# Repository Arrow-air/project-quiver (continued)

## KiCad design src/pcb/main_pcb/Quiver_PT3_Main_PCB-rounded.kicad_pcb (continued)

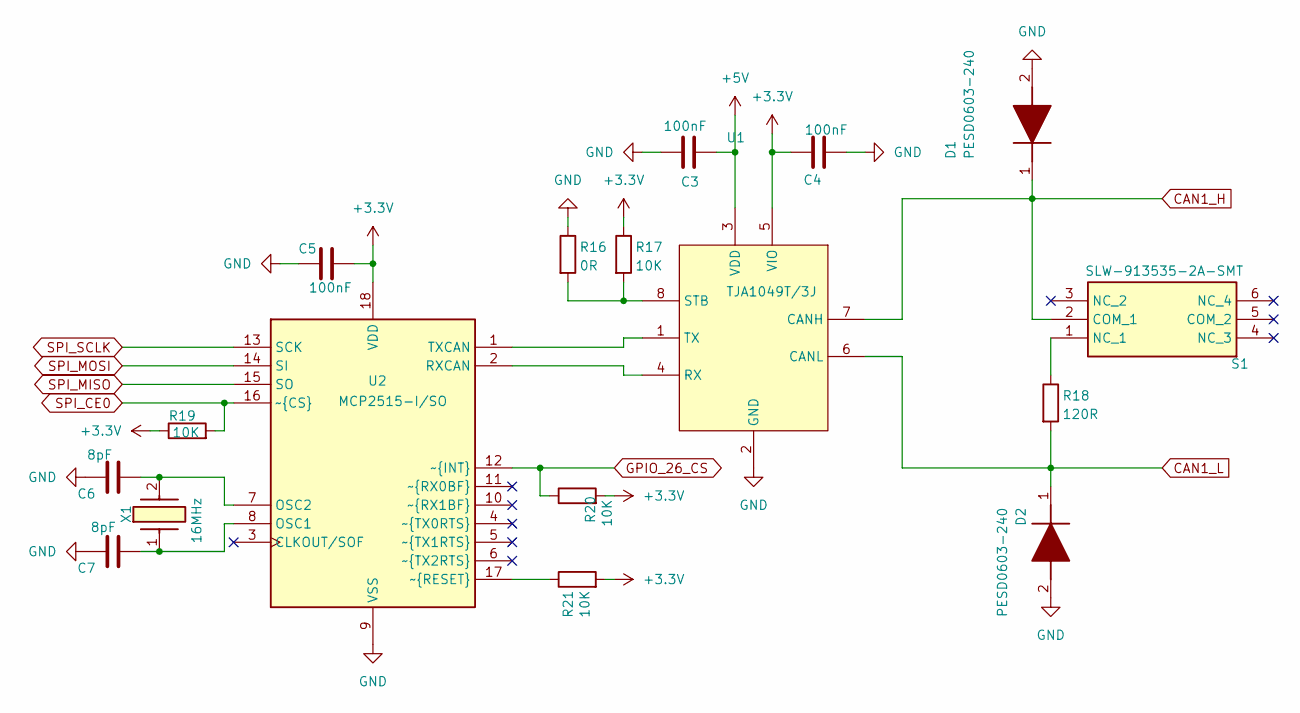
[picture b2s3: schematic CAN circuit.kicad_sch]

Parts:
C3, C4, C5: 100nF; C_0805_2012Metric_Pad1.18x1.45mm_HandSolder; MPN CC0805KRX7R9BB104
C6, C7: 8pF; C_0603_1608Metric_Pad1.08x0.95mm_HandSolder; MPN CC0603JRNPO9BN8R0
D1, D2: PESD0603-240; DIONC1608X55N; MPN PESD0603-240; Mouser Part Number 650-PESD0603-240
R16: 0R; R_0805_2012Metric_Pad1.20x1.40mm_HandSolder; MPN RC0805FR-070RL
R17, R19, R20, R21: 10K; R_0805_2012Metric_Pad1.20x1.40mm_HandSolder; MPN RC0805FR-0710KL
R18: 120R; R_0805_2012Metric_Pad1.20x1.40mm_HandSolder; MPN RC0805FR-07120RL
S1: SLW-913535-2A-SMT; SLW9135352ASMT; MPN SLW-913535-2A-SMT; Mouser Part Number 179-SLW-913535-2ASMT
U1: TJA1049T/3J; SOIC127P600X175-8N; MPN TJA1049T/3J; Mouser Part Number 771-TJA1049T/3J
U2: MCP2515-I/SO; SOIC127P1030X265-18N; MPN MCP2515-I/SO; Mouser Part Number 579-MCP2515-I/SO
X1: 16MHz; NX3225GB-16M-STD-CRA-2; MPN NX3225GB-16M-STD-CRA-2; Mouser Part Number 344-NX3225GB16MSTRA2

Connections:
+3.3V: C4.1, C5.2, R17.1, R19.1, R20.2, R21.2, U1.5 (VIO), U2.18 (VDD); also elsewhere on the board
+5V: C3.2, U1.3 (VDD); also elsewhere on the board
CAN1_H: D1.1 (K), S1.2 (COM_1), U1.7 (CANH); also elsewhere on the board
CAN1_L: D2.1 (K), R18.2, U1.6 (CANL); also elsewhere on the board
GND: C3.1, C4.2, C5.1, C6.1, C7.1, D1.2 (A), D2.2 (A), R16.1, U1.2 (GND), U2.9 (VSS); also elsewhere on the board
GPIO_26_CS: R20.1, U2.12 (~INT~{}); also elsewhere on the board
unnamed: R18.1, S1.1 (NC_1)
unnamed: U1.4 (RX), U2.2 (RXCAN)
unnamed: R16.2, R17.2, U1.8 (STB)
unnamed: U1.1 (TX), U2.1 (TXCAN)
unnamed: C7.2, U2.8 (OSC1), X1.1
unnamed: C6.2, U2.7 (OSC2), X1.2
unnamed: R21.1, U2.17 (~RESET~{})
SPI_CE0: R19.2, U2.16 (~CS~{}); also elsewhere on the board
SPI_MISO: U2.15 (SO); also elsewhere on the board
SPI_MOSI: U2.14 (SI); also elsewhere on the board
SPI_SCLK: U2.13 (SCK); also elsewhere on the board

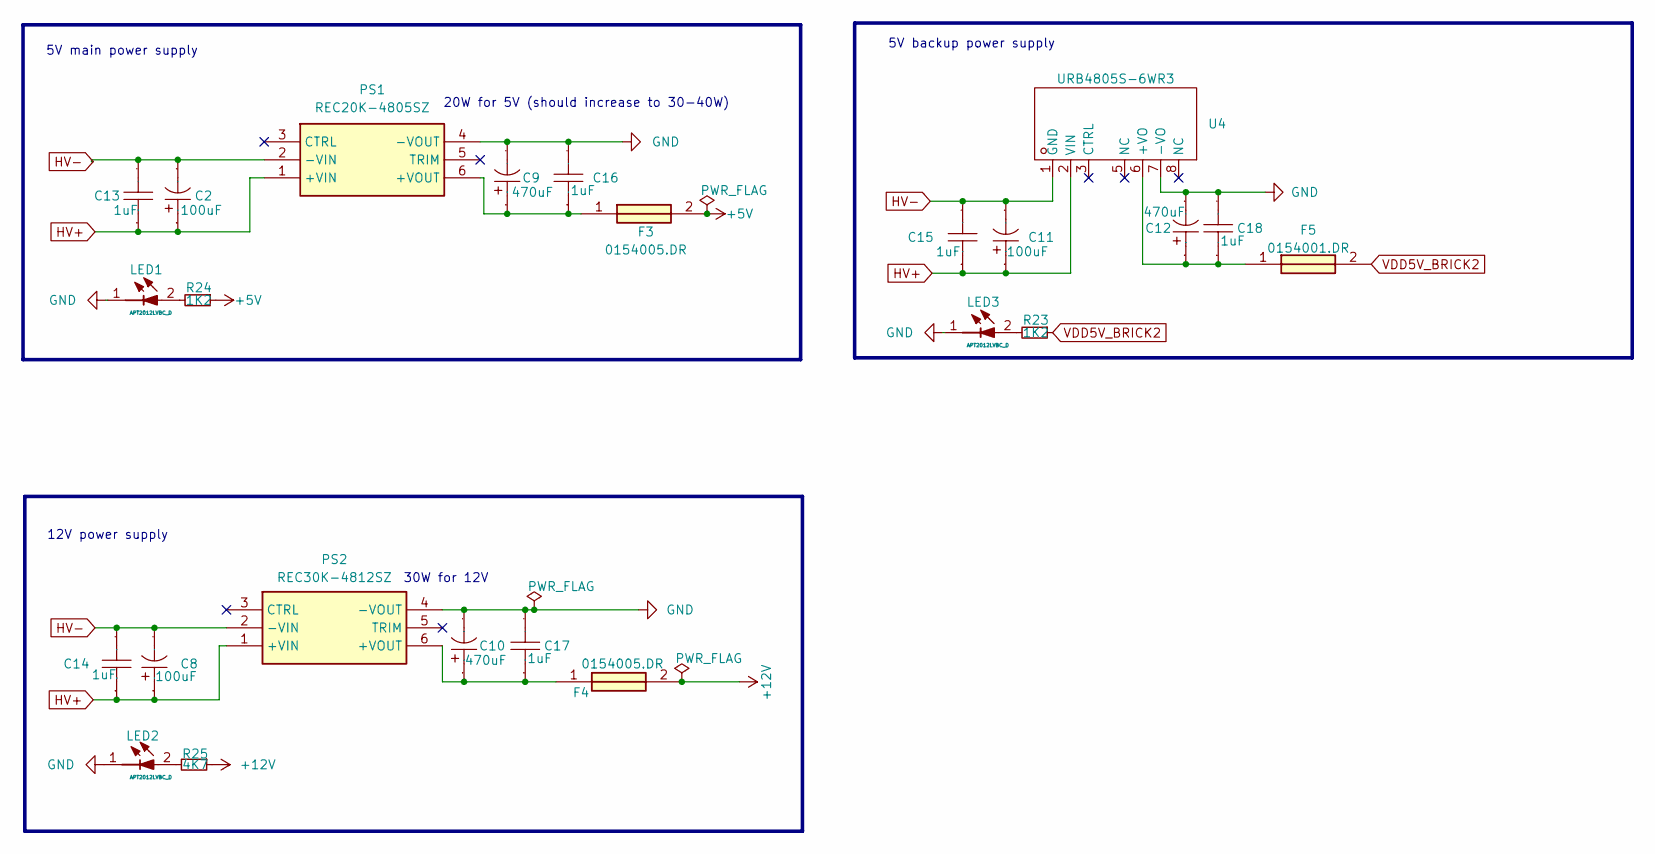
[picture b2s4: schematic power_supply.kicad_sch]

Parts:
C2, C8, C11: 100uF; CAP-TH_BD10.0-P5.00-D0.6-FD_2; Manufacturer Part 1011001013R00; LCSC Part Name 100uF ±20% 100V
C9, C10, C12: 470uF; CAP-TH_BD8.0-P3.50-D0.6-FD; Manufacturer Part SPT1EM471F12OR; LCSC Part Name 470uF ±20% 25V
C13, C14, C15, C16, C17, C18: 1uF; C1206; Manufacturer Part CL31B105KCHNNNE; LCSC Part Name 1uF ±10% 100V
F3, F4: 0154005.DR; 0154005DR; Mouser Part Number 576-0154005.DR
F5: 0154001.DR; 0154001DR; Mouser Part Number 576-0154001.DR
LED1, LED2, LED3: APT2012LVBC_D; LEDC2012X85N; Mouser Part Number 604-APT2012LVBCD
PS1: REC20K-4805SZ; REC20K; Manufacturer_Part_Number REC20K-4805SZ
PS2: REC30K-4812SZ; REC30K; Manufacturer_Part_Number REC30K-4812SZ
R23, R24: 1K2; R_0805_2012Metric_Pad1.20x1.40mm_HandSolder
R25: 4K7; R_0805_2012Metric_Pad1.20x1.40mm_HandSolder
U4: URB4805S-6WR3; PWRM-TH_YLPTEC_URBXXXXS-6WR3; Manufacturer Part URB4805S-6WR3; LCSC Part Name DC/DC电源模块 6W宽压输入，隔离稳压单路/正负双路输出

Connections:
+5V: F3.2, R24.1; also elsewhere on the board
+12V: F4.2, R25.1; also elsewhere on the board
GND: C9.2, C10.2, C12.2, C16.2, C17.2, C18.2, LED1.1 (K), LED2.1 (K), LED3.1 (K), PS1.4 (-VOUT), PS2.4 (-VOUT), U4.7 (-VO); also elsewhere on the board
HV+: C2.1, C8.1, C11.1, C13.1, C14.1, C15.1, PS1.1 (+VIN), PS2.1 (+VIN), U4.2 (VIN); also elsewhere on the board
HV-: C2.2, C8.2, C11.2, C13.2, C14.2, C15.2, PS1.2 (-VIN), PS2.2 (-VIN), U4.1 (GND); also elsewhere on the board
unnamed: LED1.2 (A), R24.2
unnamed: LED2.2 (A), R25.2
unnamed: LED3.2 (A), R23.2
unnamed: C9.1, C16.1, F3.1, PS1.6 (+VOUT)
unnamed: C10.1, C17.1, F4.1, PS2.6 (+VOUT)
unnamed: C12.1, C18.1, F5.1, U4.6 (+VO)
VDD5V_BRICK2: F5.2, R23.1; also elsewhere on the board

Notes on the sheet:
5V backup power supply
5V main power supply
30W for 12V
12V power supply
20W for 5V (should increase to 30-40W)

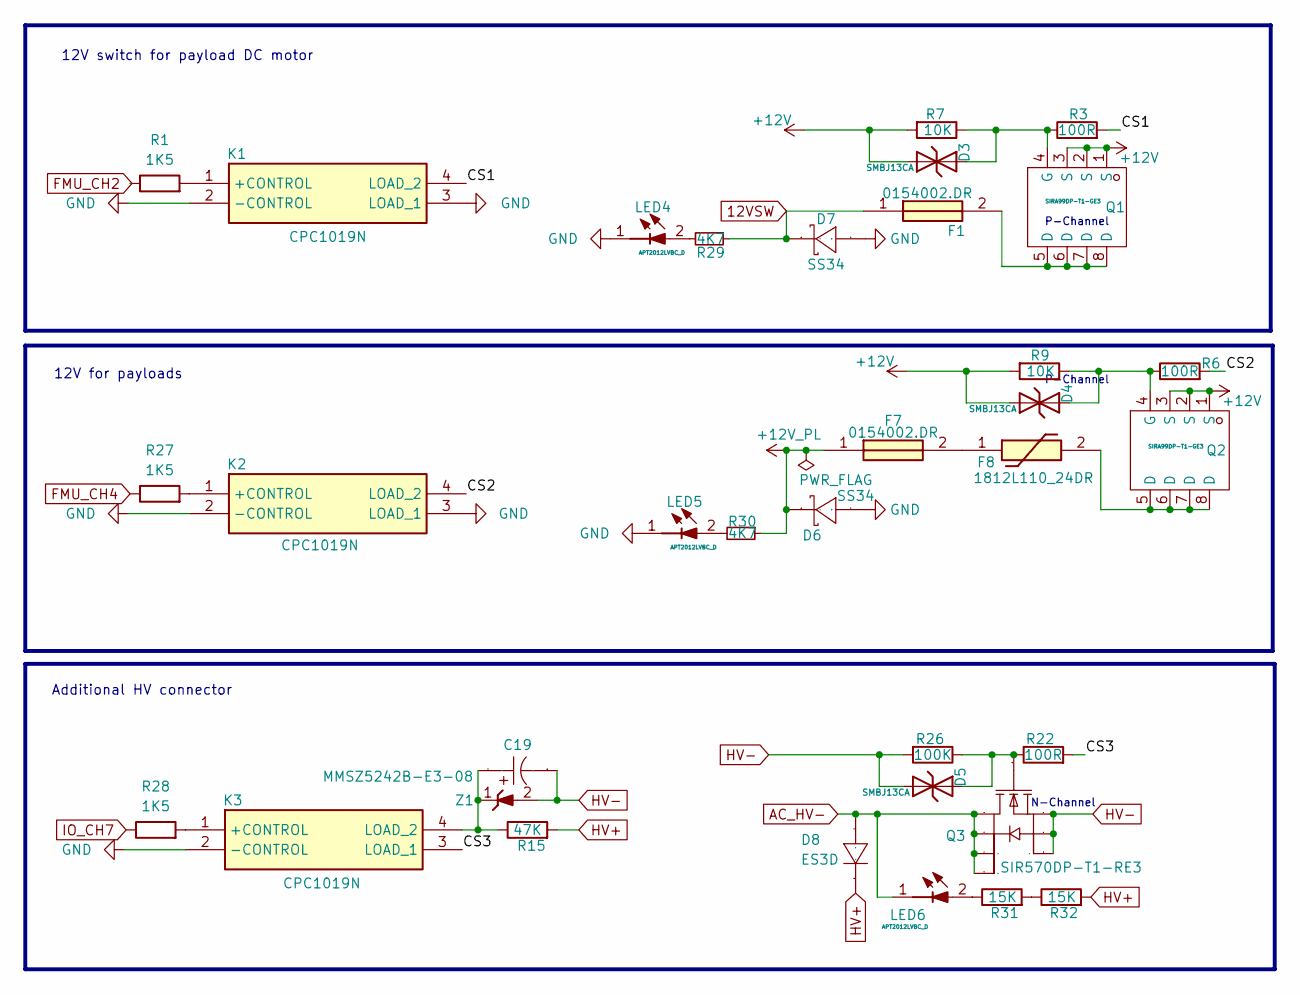
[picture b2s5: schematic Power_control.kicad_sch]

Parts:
C19: 22uF; CAP-SMD_L7.3-W4.3-RD_PA300LV227M0J; Manufacturer Part EEFCX1E220R; LCSC Part Name 22uF ±20% 25V
D3, D4, D5: SMBJ13CA; D_SMB; Part SMBJ13CA; LCSC C19077568
D6, D7: SS34; SMB_L4.6-W3.6-LS5.3-RD; Manufacturer Part SS34; LCSC Part Name 电压:40V 电流:3A
D8: ES3D; SMC_L7.1-W6.2-LS8.1-RD; Manufacturer Part ES3D; LCSC Part Name ES3D
F1, F7: 0154002.DR; 0154002DR; Mouser Part Number 576-0154002.DR
F8: 1812L110_24DR; 1812L010DR; Mouser Part Number 576-1812L110/24DR
K1, K2, K3: CPC1019N; SOP254P610X218-4N; Mouser Part Number 849-CPC1019N
LED4, LED5, LED6: APT2012LVBC_D; LEDC2012X85N; Mouser Part Number 604-APT2012LVBCD
Q1, Q2: SIRA99DP-T1-GE3; POWERPAK-SO-8_L5.9-W4.9-P1.27-LS6.2-BL; Mouser Part Number 781-SIR804DP-T1-GE3
Q3: SIR570DP-T1-RE3; POWERPAK-SO-8_L5.9-W4.9-P1.27-LS6.2-BL; Mouser Part Number 781-SIR804DP-T1-GE3
R1, R27, R28: 1K5; R_0805_2012Metric_Pad1.20x1.40mm_HandSolder
R3, R6, R22: 100R; R_0805_2012Metric_Pad1.20x1.40mm_HandSolder
R7, R9: 10K; R_0805_2012Metric_Pad1.20x1.40mm_HandSolder
R15: 47K; R_0805_2012Metric_Pad1.20x1.40mm_HandSolder
R26: 100K; R_0805_2012Metric_Pad1.20x1.40mm_HandSolder
R29, R30: 4K7; R_0805_2012Metric_Pad1.20x1.40mm_HandSolder
R31, R32: 15K; R_0805_2012Metric_Pad1.20x1.40mm_HandSolder
Z1: MMSZ5242B-E3-08; SOD3716X135N; Mouser Part Number 78-MMSZ5242B-E3-08

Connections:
12VSW: D7.1 (C), F1.1, R29.1; also elsewhere on the board
+12V: D3.1, D4.1, Q1.1 (S), Q1.2 (S), Q1.3 (S), Q2.1 (S), Q2.2 (S), Q2.3 (S), R7.2, R9.2; also elsewhere on the board
+12V_PL: D6.1 (C), F7.1, R30.1; also elsewhere on the board
/Power_control/CS1: K1.4 (LOAD_2), R3.2
/Power_control/CS2: K2.4 (LOAD_2), R6.2
/Power_control/CS3: K3.3 (LOAD_1), R22.2
AC_HV-: D8.2, LED6.1 (K), Q3.5 (D), Q3.6 (D), Q3.7 (D), Q3.8 (D); also elsewhere on the board
FMU_CH2: R1.1; also elsewhere on the board
FMU_CH4: R27.1; also elsewhere on the board
GND: D6.2 (A), D7.2 (A), K1.2 (-CONTROL), K1.3 (LOAD_1), K2.2 (-CONTROL), K2.3 (LOAD_1), K3.2 (-CONTROL), LED4.1 (K), LED5.1 (K); also elsewhere on the board
HV+: D8.1, R15.2, R32.2; also elsewhere on the board
HV-: C19.1, D5.1, Q3.1 (S), Q3.2 (S), Q3.3 (S), R26.2, Z1.2 (A); also elsewhere on the board
IO_CH7: R28.1; also elsewhere on the board
unnamed: F1.2, Q1.5 (D), Q1.6 (D), Q1.7 (D), Q1.8 (D)
unnamed: F7.2, F8.1
unnamed: F8.2, Q2.5 (D), Q2.6 (D), Q2.7 (D), Q2.8 (D)
unnamed: K1.1 (+CONTROL), R1.2
unnamed: K2.1 (+CONTROL), R27.2
unnamed: K3.1 (+CONTROL), R28.2
unnamed: C19.2, K3.4 (LOAD_2), R15.1, Z1.1 (K)
unnamed: LED4.2 (A), R29.2
unnamed: LED5.2 (A), R30.2
unnamed: LED6.2 (A), R31.1
unnamed: D3.2, Q1.4 (G), R3.1, R7.1
unnamed: D4.2, Q2.4 (G), R6.1, R9.1
unnamed: D5.2, Q3.4 (G), R22.1, R26.1
unnamed: R31.2, R32.1

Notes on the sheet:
Additional HV connector
12V switch for payload DC motor
P-Channel
N-Channel
12V for payloads

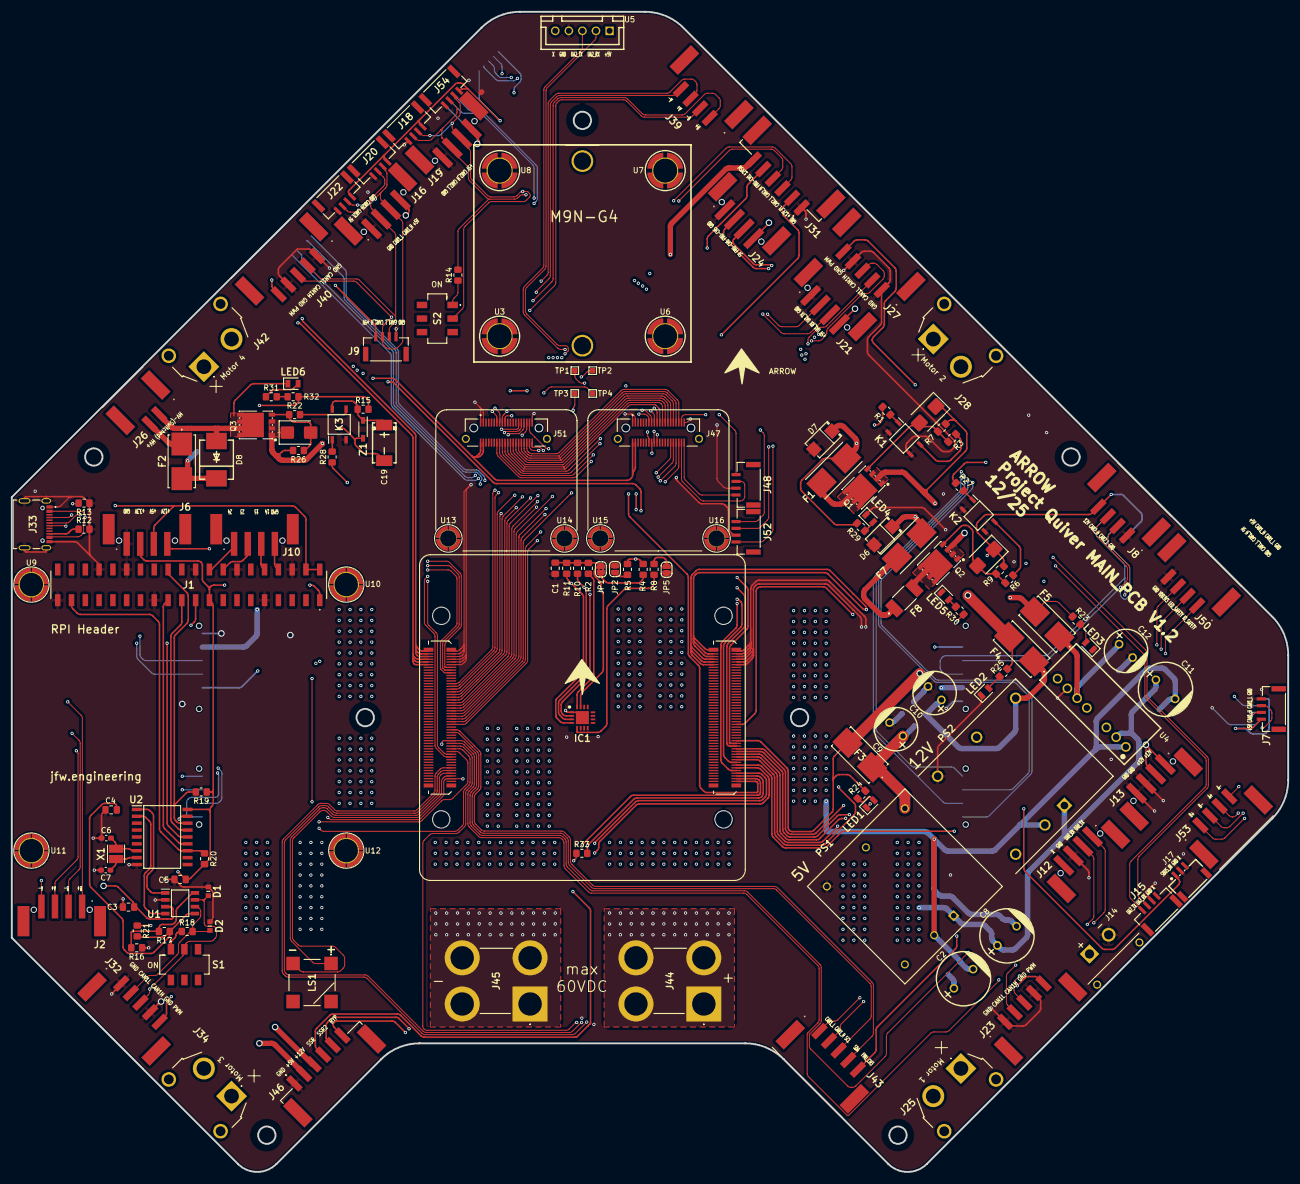
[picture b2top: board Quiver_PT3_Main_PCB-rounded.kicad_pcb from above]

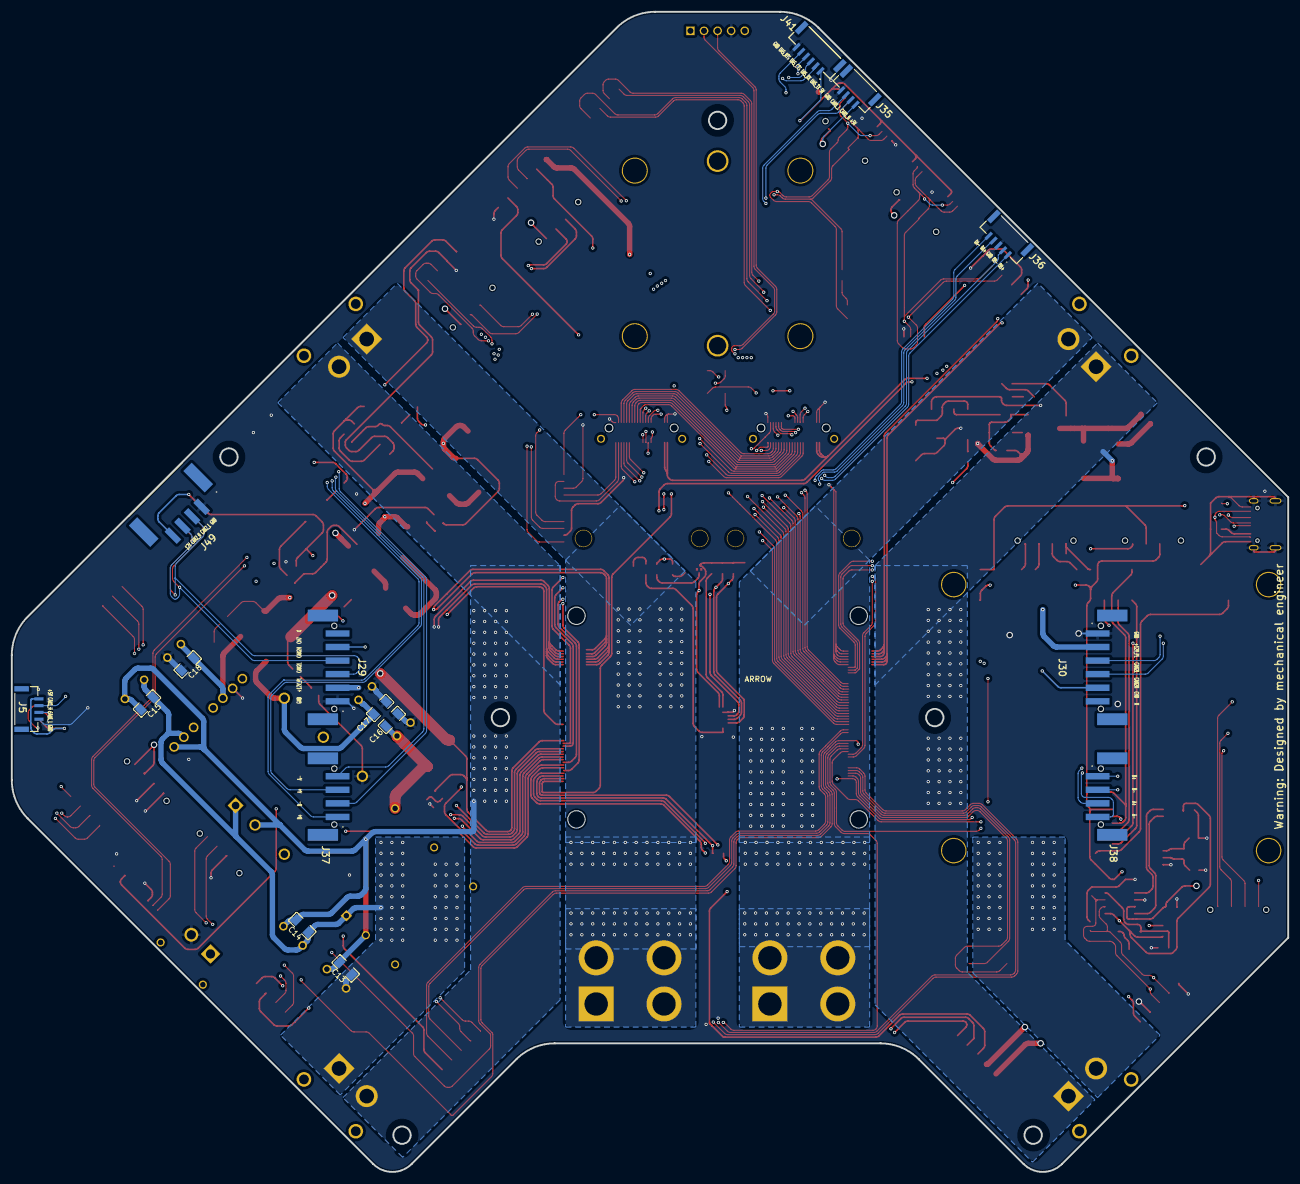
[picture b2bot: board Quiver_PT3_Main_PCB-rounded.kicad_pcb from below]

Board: 6 copper layers, 235.1 x 213.7 mm, 164 parts (15 on the bottom side), 146 nets.

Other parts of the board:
U13, U14, U15, U16: SMTWEM245STR; SCREW-SMD_BD4.4-D2.8-H4.5

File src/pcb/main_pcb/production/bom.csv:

Designator,Footprint,Quantity,Value,LCSC Part #
"C1, C2, C3, C4, C5",0805,5,100nF,CC0805KRX7R9BB104
"C6, C7",0603,2,8pF,CC0603JRNPO9BN8R0
"D1, D2",DIONC1608X55N,2,PESD0603-240,PESD0603-240
"F1, F7",0154002DR,2,0154002.DR,
"F2, F3, F4",0154005DR,3,0154005.DR,
F8,1812L010DR,1,1812L110_24DR,
"IC1, IC2",QFN65P400X400X90-17N,2,TSYS01,
J1,SSM-120-XXX-DV,1,RPI_5_WITH_SSQ-120-01-F-D,
"J10, J12, J13, J16, J19, J21, J24, J37, J38, J50, J53, J6, J9",1778719,13,1778719,
J11,M9N-G4-3100,1,M9N-G4-3100,
J14,XT30PW-F_AMASS_XT30PW-F,1,XT30PW-F,
"J15, J2, J22, J39, J49, J5, J7, J8",1814935,8,1814935,
J17,1814922,1,1814922,
"J23, J27, J32, J40, J43",1814948,5,1814948,
"J25, J28, J34, J42",XT60PWF,4,XT60PW-F,
J26,1814919,1,1814919,
"J29, J30",1778735,2,1778735,
"J3, J4",AXK6S00547YG,2,AXK6S00547YG,
"J31, J46",1814951,2,1814951,
J33,USB421603A,1,USB4216-03-A,
"J35, J48, J52",SM04B-GHS-TB,3,SM04B-GHS-TB_LF__SN_,
J36,SM05B-GHS-TB,1,SM05B-GHS-TB_LF__SN_,
J41,SM06B-GHS-TB,1,SM06B-GHS-TB_LF__SN_,
"J44, J45",AMT0450003DB0000G,2,AMT0450003DB0000G,
"J47, J51",GIGABLOX_NANO_SWITCH_REVA_MODULE_LSHM-120-02.5-L-DV-A-S-K-TR,2,GIGABLOX_NANO_SWITCH_REVA_MODULE,
K1,SOP254P610X218-4N,1,CPC1019N,
"LED1, LED2",LEDC2012X85N,2,APT2012LVBC_D,
LS1,CMT8530SSMTTR,1,CMT-8530S-SMT-TR,
PS1,REC20K,1,REC20K-4805SZ,
PS2,REC30K,1,REC30K-4812SZ,
"R1, R15, R23",0805,3,1K5,
"R10, R11, R17, R19, R20, R21",0805,6,10k,RC0805FR-0710KL
"R12, R13",0805,2,5K1,
"R14, R18",0805,2,120R,RC0805FR-07120RL
R16,0805,1,0R,RC0805FR-070RL
"R2, R3, R4, R5, R6",0805,5,100k,
R24,0805,1,1K2,
R25,0805,1,4K7,
R7,0805,1,100k,RC0805FR-070RL
R8,0805,1,100k,RC0805FR-0710KL
R9,0805,1,100k,RC0805FR-07120RL
"S1, S2",SLW9135352ASMT,2,SLW-913535-2A-SMT,SLW-913535-2A-SMT
"TP1, TP2, TP3, TP4",TestPoint_Pad_1.0x1.0mm,4,TestPoint_Small,
U1,SOIC127P600X175-8N,1,TJA1049T/3J,TJA1049T/3J
U2,SOIC127P1030X265-18N,1,MCP2515-I/SO,MCP2515-I/SO
"U4, U5",CPC1907B,2,CPC1907B,
X1,NX3225GD-STD-CRA-3,1,16MHz,NX3225GB-16M-STD-CRA-2

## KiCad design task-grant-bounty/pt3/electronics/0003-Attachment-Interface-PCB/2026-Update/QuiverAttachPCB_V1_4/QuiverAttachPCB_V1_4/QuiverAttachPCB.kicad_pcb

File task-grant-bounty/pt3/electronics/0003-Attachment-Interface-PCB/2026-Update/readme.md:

This updated PCB design retains all of the features of the original design with slight modifications. 
Notable updates:
- Front and rear solder pads extended to improve manufacturing 
- J2 and J3 Removed
- J2 replaced with U1 - U10, individual spring loaded pin headers 
- J3 replaced with U11 - U20, larger solder pads to interface with the spring loaded pins
- updated routing with rounded edges
- notch image added to indicate proper orientation relative to the quick release interface 

Design updates by Julius

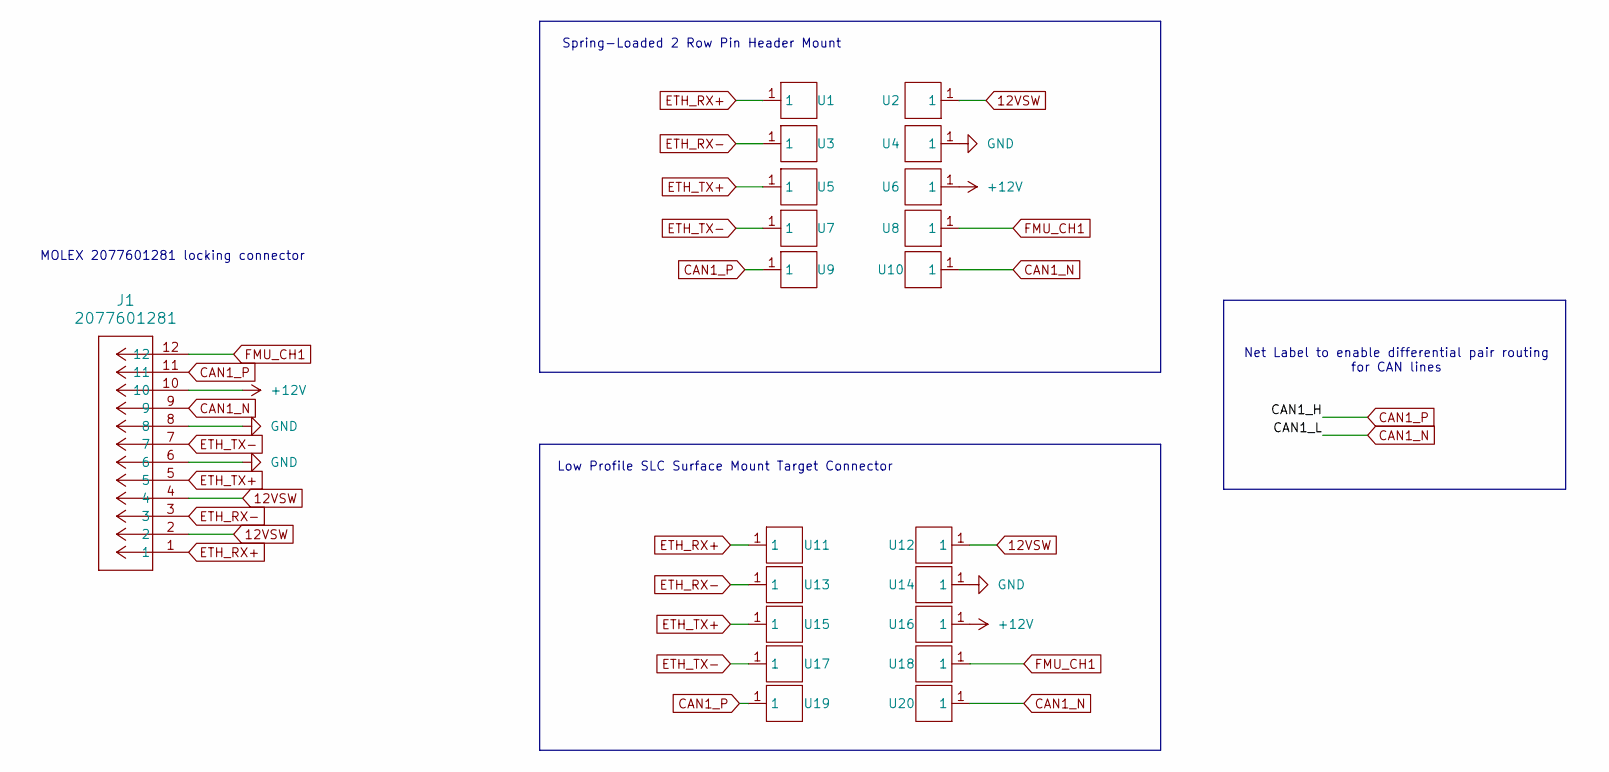
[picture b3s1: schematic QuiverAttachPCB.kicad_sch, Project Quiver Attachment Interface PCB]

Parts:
J1: 2077601281; CONN12_2077601281_MOL
U1, U2, U3, U4, U5, U6, U7, U8, U9, U10: C2826546-BWCD-L4.5W2.0H2.3; Manufacturer Part BWCD-L4.5W2.0H2.3; LCSC Part Name POGO PIN
U11, U12, U13, U14, U15, U16, U17, U18, U19, U20: C2826546-BWCD-L4.5W2.0H2.3_only_Pad_D2.0mm_1; Manufacturer Part BWCD-L4.5W2.0H2.3; LCSC Part Name POGO PIN

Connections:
12VSW: J1.2, J1.4, U2.1, U12.1
+12V: J1.10, U6.1, U16.1
CAN1_N: J1.9, U10.1, U20.1
CAN1_P: J1.11, U9.1, U19.1
ETH_RX+: J1.1, U1.1, U11.1
ETH_RX-: J1.3, U3.1, U13.1
ETH_TX+: J1.5, U5.1, U15.1
ETH_TX-: J1.7, U7.1, U17.1
FMU_CH1: J1.12, U8.1, U18.1
GND: J1.6, J1.8, U4.1, U14.1

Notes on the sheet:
MOLEX 2077601281 locking connector
Spring-Loaded 2 Row Pin Header Mount
Low Profile SLC Surface Mount Target Connector
Net Label to enable differential pair routing for CAN lines

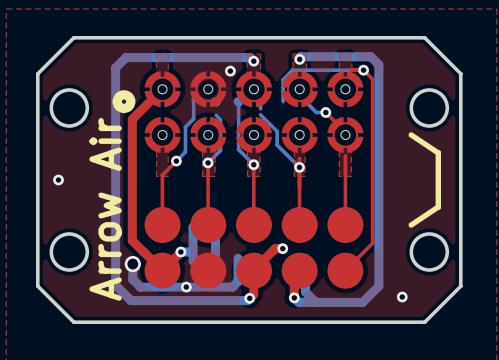
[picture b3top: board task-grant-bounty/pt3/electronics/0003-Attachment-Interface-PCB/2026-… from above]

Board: 2 copper layers, 23.5 x 15.8 mm, 21 parts (1 on the bottom side), 10 nets.

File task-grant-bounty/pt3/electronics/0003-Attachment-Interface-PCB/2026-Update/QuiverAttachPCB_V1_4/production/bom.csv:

Designator,Footprint,Quantity,Value,LCSC Part #
J1,CONN12_2077601281_MOL,1,2077601281,
"U1, U10, U2, U3, U4, U5, U6, U7, U8, U9",C2826546-BWCD-L4.5W2.0H2.3,10,~,
"U11, U12, U13, U14, U15, U16, U17, U18, U19, U20",C2826546-BWCD-L4.5W2.0H2.3_only_Pad_D2.0mm_1,10,~,

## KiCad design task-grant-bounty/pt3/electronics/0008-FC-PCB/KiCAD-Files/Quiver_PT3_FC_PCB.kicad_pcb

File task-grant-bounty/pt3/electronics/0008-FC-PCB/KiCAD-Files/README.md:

# KiCad files moved

The KiCad sources for this board now live at
[`src/pcb/fc_pcb/`](../../../../../src/pcb/fc_pcb/) — see that directory for
the current design files. This folder retains the bounty task history.

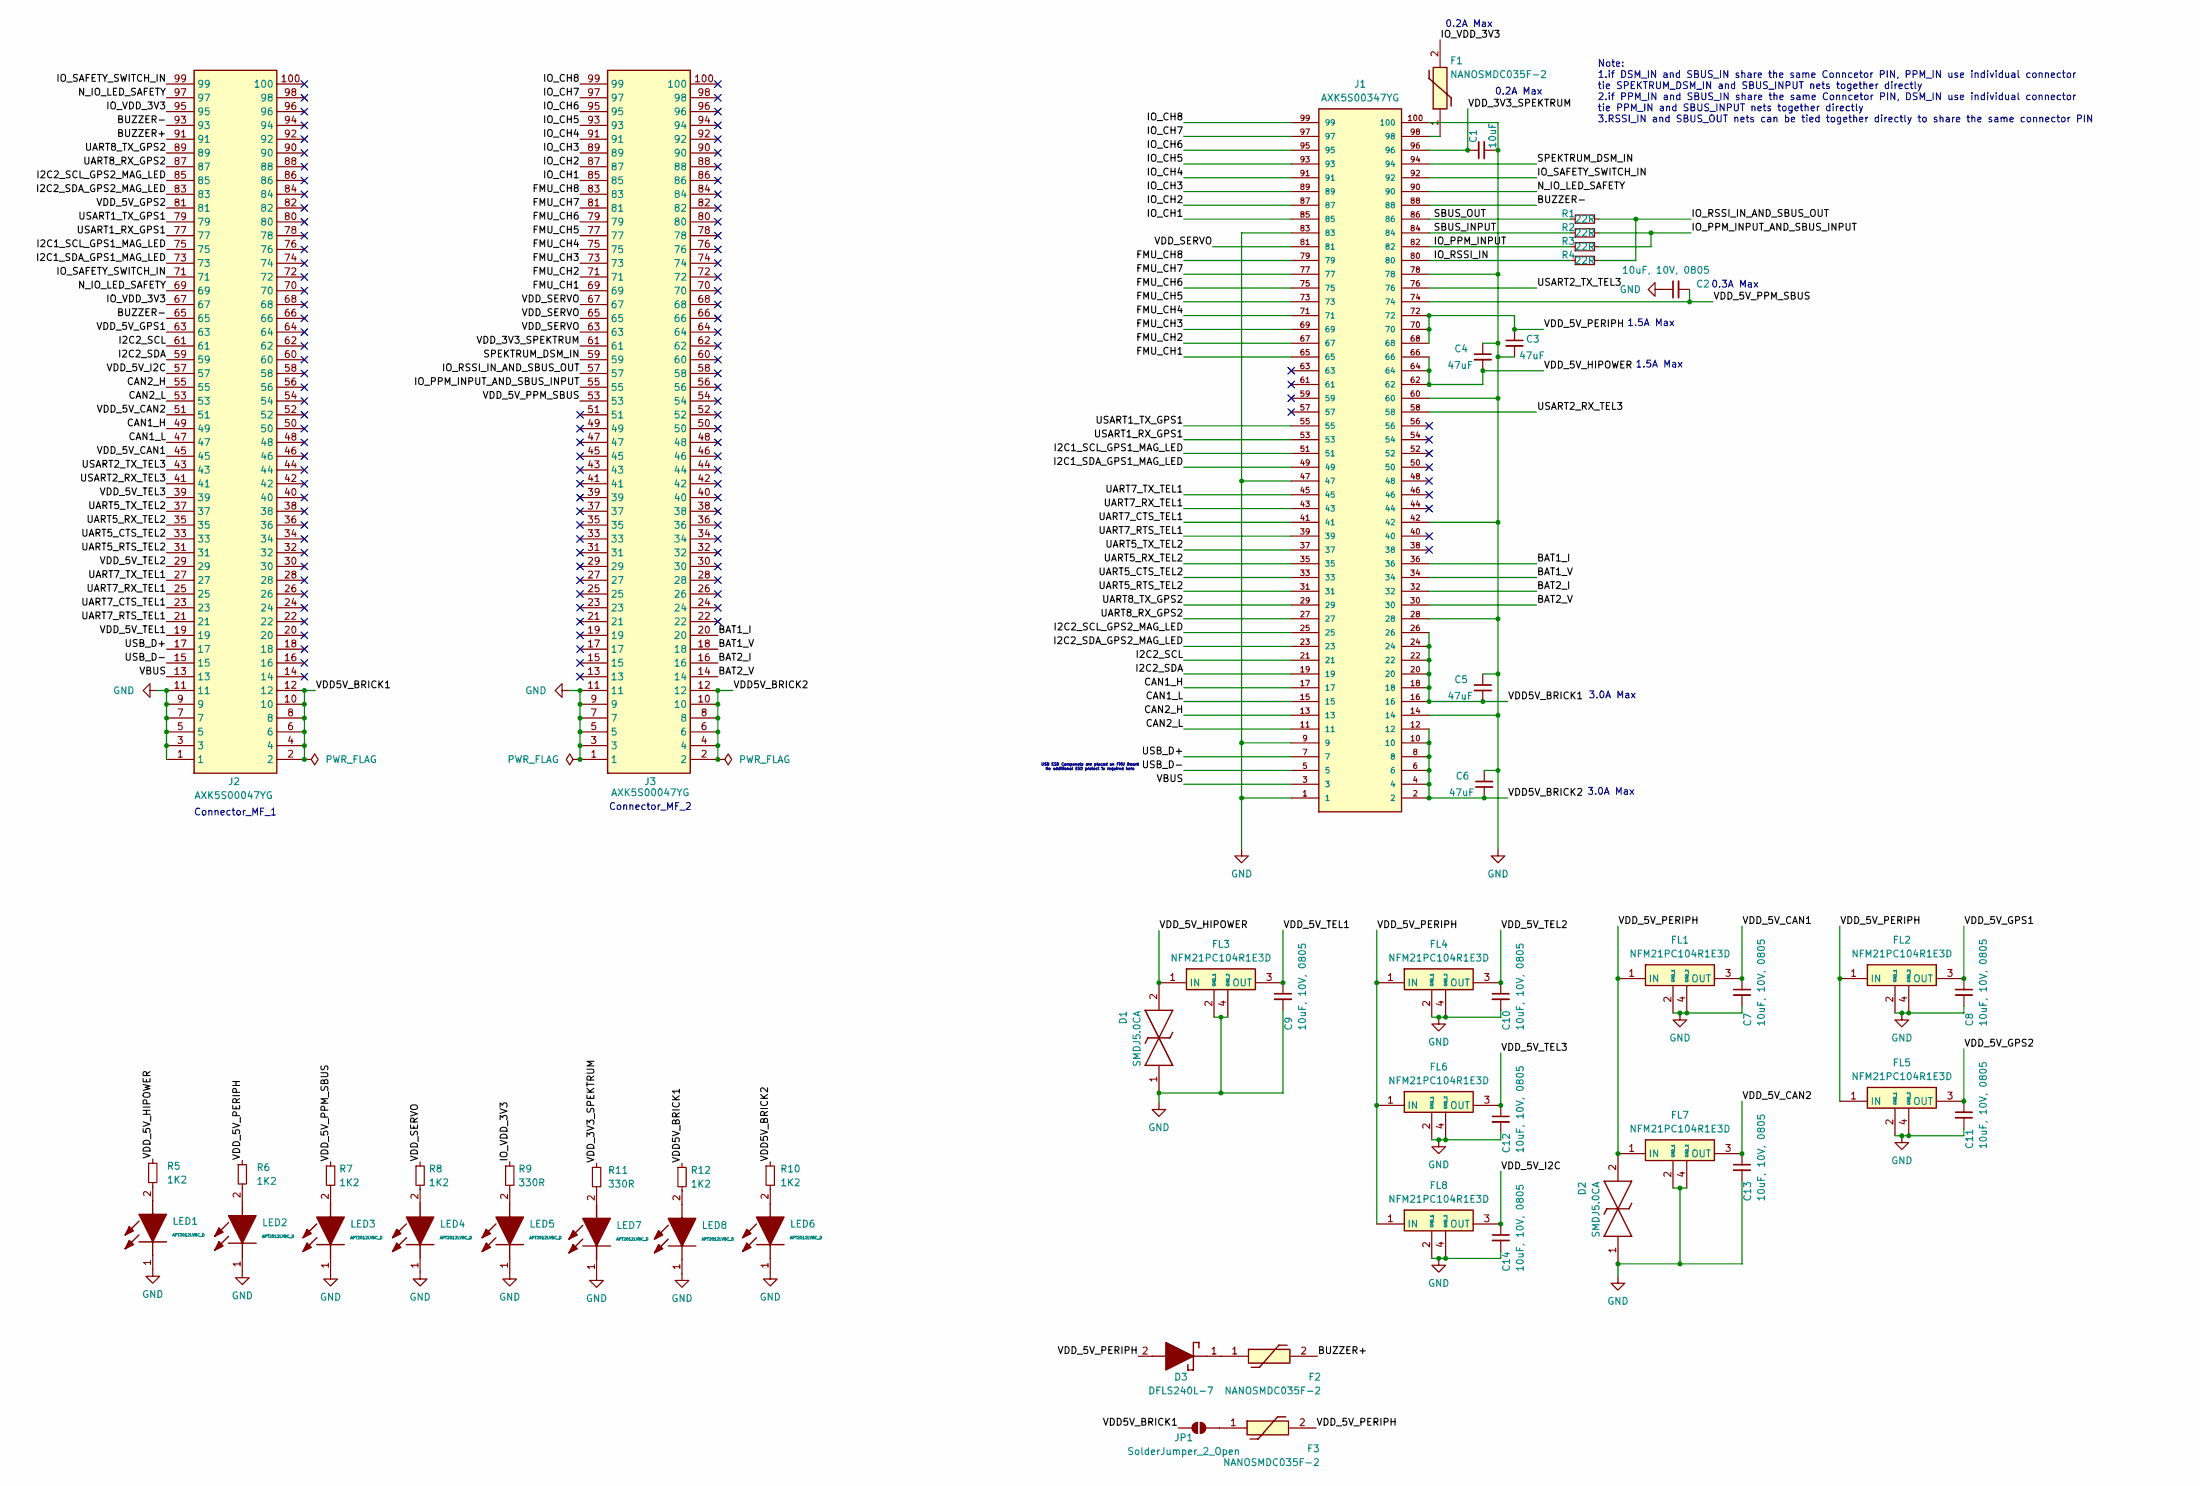
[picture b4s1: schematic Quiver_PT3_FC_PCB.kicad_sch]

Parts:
C1: 10uF; C_0805_2012Metric_Pad1.18x1.45mm_HandSolder
C2, C7, C8, C9, C10, C11, C12, C13, C14: 10uF, 10V, 0805; C_0805_2012Metric_Pad1.18x1.45mm_HandSolder
C3, C4, C5, C6: 47uF; C_0805_2012Metric_Pad1.18x1.45mm_HandSolder
D1, D2: SMDJ5.0CA; DIONM7959X262N; Mouser Part Number 576-SMDJ5.0CA
D3: DFLS240L-7; DFLS240L7; Mouser Part Number 621-DFLS240L-7
F1, F2, F3: NANOSMDC035F-2; NANOSMDC016F2; Mouser Part Number 650-NANOSMDC035F-2
FL1, FL2, FL3, FL4, FL5, FL6, FL7, FL8: NFM21PC104R1E3D; Mouser Part Number 81-NFM21PC104R1E3D
J1: AXK5S00347YG; AXK5S00347YG_AXK5S00347YG; MANUFACTURER_PART_NUMBER AXK5S00347YG
J2, J3: AXK5S00047YG; Mouser Part Number AXK5S00047YG
JP1: SolderJumper_2_Open; SolderJumper-2_P1.3mm_Open_RoundedPad1.0x1.5mm
LED1, LED2, LED3, LED4, LED5, LED6, LED7, LED8: APT2012LVBC_D; LEDC2012X85N; Mouser Part Number 604-APT2012LVBCD
R1, R2, R3, R4: 22R; R_0805_2012Metric_Pad1.20x1.40mm_HandSolder
R5, R6, R7, R8, R10, R12: 1K2; R_0805_2012Metric_Pad1.20x1.40mm_HandSolder
R9, R11: 330R; R_0805_2012Metric_Pad1.20x1.40mm_HandSolder

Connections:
/ I2C2_SDA_GPS2_MAG_LED: J1.23, J2.83
/BAT1_I: J1.36, J3.20
/BAT1_V: J1.34, J3.18
/BAT2_I: J1.32, J3.16
/BAT2_V: J1.30, J3.14
/BUZZER+: F2.2, J2.91
/BUZZER-: J1.88, J2.65, J2.93
/CAN1_H: J1.17, J2.49
/CAN1_L: J1.15, J2.47
/CAN2_H: J1.13, J2.55
/CAN2_L: J1.11, J2.53
/FMU_CH1: J1.65, J3.69
/FMU_CH2: J1.67, J3.71
/FMU_CH3: J1.69, J3.73
/FMU_CH4: J1.71, J3.75
/FMU_CH5: J1.73, J3.77
/FMU_CH6: J1.75, J3.79
/FMU_CH7: J1.77, J3.81
/FMU_CH8: J1.79, J3.83
/I2C1_SCL_GPS1_MAG_LED: J1.51, J2.75
/I2C1_SDA_GPS1_MAG_LED: J1.49, J2.73
/I2C2_SCL: J1.21, J2.61
/I2C2_SCL_GPS2_MAG_LED: J1.25, J2.85
/I2C2_SDA: J1.19, J2.59
/IO_CH1: J1.85, J3.85
/IO_CH2: J1.87, J3.87
/IO_CH3: J1.89, J3.89
/IO_CH4: J1.91, J3.91
/IO_CH5: J1.93, J3.93
/IO_CH6: J1.95, J3.95
/IO_CH7: J1.97, J3.97
/IO_CH8: J1.99, J3.99
/IO_PPM_INPUT: J1.82, R3.1
/IO_PPM_INPUT_AND_SBUS_INPUT: J3.55, R2.2, R3.2
/IO_RSSI_IN: J1.80, R4.1
/IO_RSSI_IN_AND_SBUS_OUT: J3.57, R1.2, R4.2
/IO_SAFETY_SWITCH_IN: J1.92, J2.71, J2.99
/IO_VDD_3V3: F1.2, J2.67, J2.95, R9.1
/N_IO_LED_SAFETY: J1.90, J2.69, J2.97
/SBUS_INPUT: J1.84, R2.1
/SBUS_OUT: J1.86, R1.1
/SPEKTRUM_DSM_IN: J1.94, J3.59
/UART5_CTS_TEL2: J1.33, J2.33
/UART5_RTS_TEL2: J1.31, J2.31
/UART5_RX_TEL2: J1.35, J2.35
/UART5_TX_TEL2: J1.37, J2.37
/UART7_CTS_TEL1: J1.41, J2.23
/UART7_RTS_TEL1: J1.39, J2.21
/UART7_RX_TEL1: J1.43, J2.25
/UART7_TX_TEL1: J1.45, J2.27
/UART8_RX_GPS2: J1.27, J2.87
/UART8_TX_GPS2: J1.29, J2.89
/USART1_RX_GPS1: J1.53, J2.77
/USART1_TX_GPS1: J1.55, J2.79
/USART2_RX_TEL3: J1.58, J2.41
/USART2_TX_TEL3: J1.76, J2.43
/USB_D+: J1.7, J2.17
/USB_D-: J1.5, J2.15
/VBUS: J1.3, J2.13
/VDD5V_BRICK1: C5.2, J1.16, J1.18, J1.20, J1.22, J1.24, J1.26, J2.2, J2.4, J2.6, J2.8, J2.10, J2.12, JP1.1 (A), R12.1
/VDD5V_BRICK2: C6.2, J1.2, J1.4, J1.6, J1.8, J1.10, J1.12, J3.2, J3.4, J3.6, J3.8, J3.10, J3.12, R10.1
/VDD_3V3_SPEKTRUM: C1.1, J1.96, J3.61, R11.1
/VDD_5V_CAN1: C7.1, FL1.3 (OUT), J2.45
/VDD_5V_CAN2: C13.1, FL7.3 (OUT), J2.51
/VDD_5V_GPS1: C8.1, FL2.3 (OUT), J2.63
/VDD_5V_GPS2: C11.1, FL5.3 (OUT), J2.81
/VDD_5V_HIPOWER: C4.2, D1.2, FL3.1 (IN), J1.62, J1.64, J1.66, R5.1
/VDD_5V_I2C: C14.1, FL8.3 (OUT), J2.57
/VDD_5V_PERIPH: C3.1, D2.2, D3.2 (A), F3.2, FL1.1 (IN), FL2.1 (IN), FL4.1 (IN), FL5.1 (IN), FL6.1 (IN), FL7.1 (IN), FL8.1 (IN), J1.68, J1.70, J1.72, R6.1
/VDD_5V_PPM_SBUS: C2.2, J1.74, J3.53, R7.1
/VDD_5V_TEL1: C9.1, FL3.3 (OUT), J2.19
/VDD_5V_TEL2: C10.1, FL4.3 (OUT), J2.29
/VDD_5V_TEL3: C12.1, FL6.3 (OUT), J2.39
/VDD_SERVO: J1.81, J3.63, J3.65, J3.67, R8.1
GND: C1.2, C2.1, C3.2, C4.1, C5.1, C6.1, C7.2, C8.2, C9.2, C10.2, C11.2, C12.2, C13.2, C14.2, D1.1, D2.1, FL1.2 (GND_1), FL1.4 (GND_2), FL2.2 (GND_1), FL2.4 (GND_2), FL3.2 (GND_1), FL3.4 (GND_2), FL4.2 (GND_1), FL4.4 (GND_2), FL5.2 (GND_1), FL5.4 (GND_2), FL6.2 (GND_1), FL6.4 (GND_2), FL7.2 (GND_1), FL7.4 (GND_2), FL8.2 (GND_1), FL8.4 (GND_2), J1.1, J1.9, J1.14, J1.28, J1.42, J1.47, J1.60, J1.78, J1.83, J1.100, J2.1, J2.3, J2.5, J2.7, J2.9, J2.11, J3.1, J3.3, J3.5, J3.7, J3.9, J3.11, LED1.1 (K), LED2.1 (K), LED3.1 (K), LED4.1 (K), LED5.1 (K), LED6.1 (K), LED7.1 (K), LED8.1 (K)
unnamed: D3.1 (K), F2.1
unnamed: F1.1, J1.98
unnamed: F3.1, JP1.2 (B)
unnamed: LED1.2 (A), R5.2
unnamed: LED2.2 (A), R6.2
unnamed: LED3.2 (A), R7.2
unnamed: LED4.2 (A), R8.2
unnamed: LED5.2 (A), R9.2
unnamed: LED6.2 (A), R10.2
unnamed: LED7.2 (A), R11.2
unnamed: LED8.2 (A), R12.2

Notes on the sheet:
3.0A Max
0.2A Max
0.3A Max
1.5A Max
Connector_MF_2
USB ESD Componets are placed on FMU Board No additional ESD protect is required here
Connector_MF_1
Note: 1.if DSM_IN and SBUS_IN share the same Conncetor PIN, PPM_IN use individual connector tie SPEKTRUM_DSM_IN and SBUS_INPUT nets together directly 2.if PPM_IN and SBUS_IN share the same Conncetor PIN, DSM_IN use individual connector tie PPM_IN and SBUS_INPUT nets together directly 3.RSSI_IN and 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
